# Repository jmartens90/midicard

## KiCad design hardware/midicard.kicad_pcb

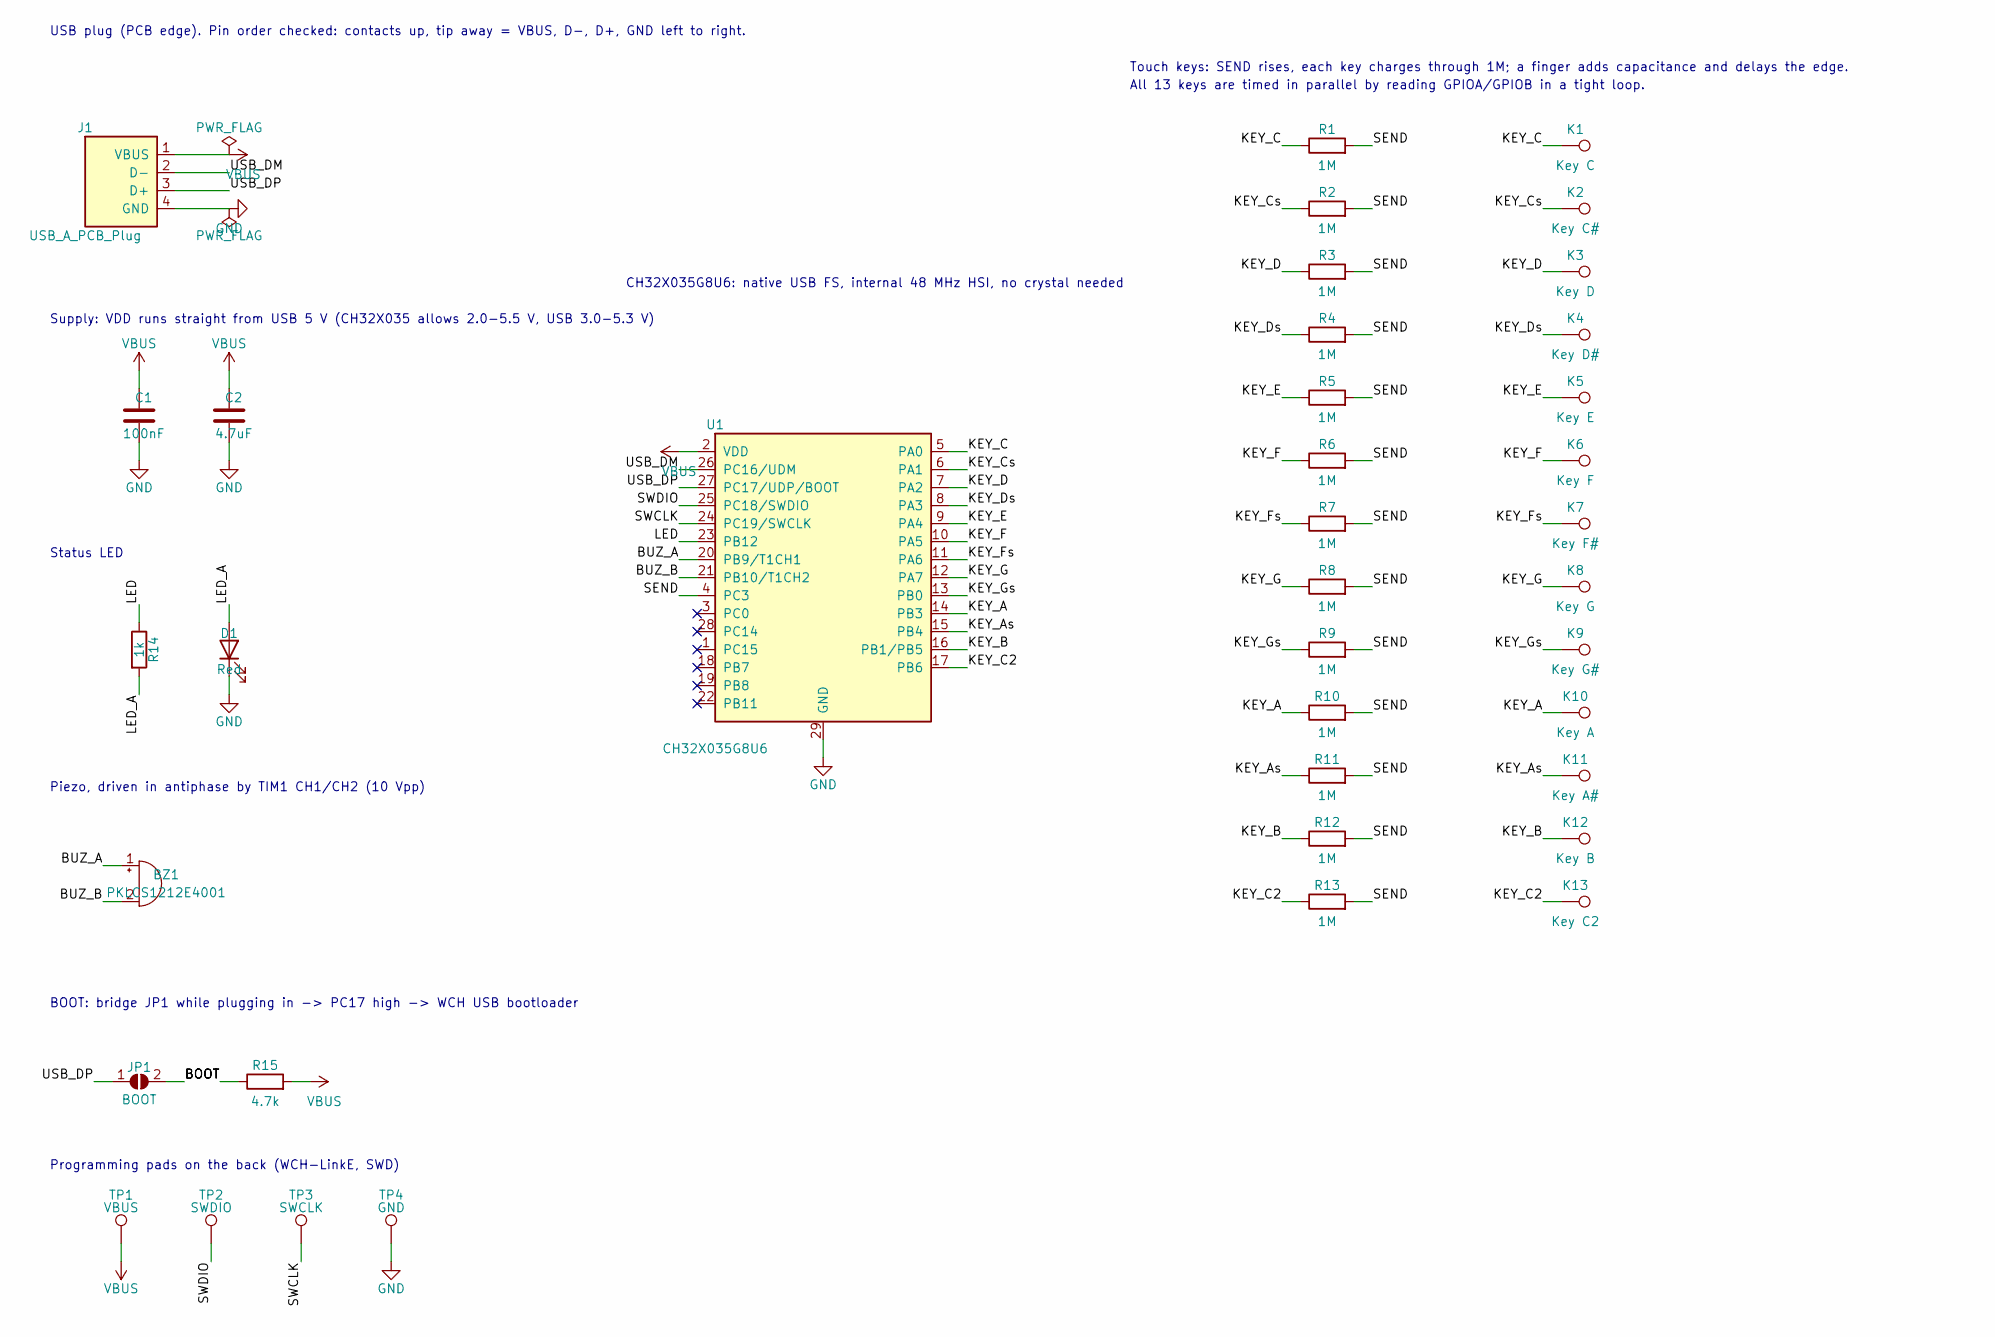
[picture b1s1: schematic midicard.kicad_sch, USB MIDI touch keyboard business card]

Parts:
BZ1: PKLCS1212E4001; Buzzer_Murata_PKLCS1212E; LCSC C113159
C1: 100nF; C_0402_1005Metric; LCSC C1525
C2: 4.7uF; C_0603_1608Metric; LCSC C19666
D1: Red; LED_0603_1608Metric; LCSC C2286
J1: USB_A_PCB_Plug
JP1: BOOT; SolderJumper-2_P1.3mm_Open_RoundedPad1.0x1.5mm
K1: Key C; TouchKey_KEY_C
K2: Key C#; TouchKey_KEY_Cs
K3: Key D; TouchKey_KEY_D
K4: Key D#; TouchKey_KEY_Ds
K5: Key E; TouchKey_KEY_E
K6: Key F; TouchKey_KEY_F
K7: Key F#; TouchKey_KEY_Fs
K8: Key G; TouchKey_KEY_G
K9: Key G#; TouchKey_KEY_Gs
K10: Key A; TouchKey_KEY_A
K11: Key A#; TouchKey_KEY_As
K12: Key B; TouchKey_KEY_B
K13: Key C2; TouchKey_KEY_C2
R1, R2, R3, R4, R5, R6, R7, R8, R9, R10, R11, R12, R13: 1M; R_0402_1005Metric; LCSC C26083
R14: 1k; R_0402_1005Metric; LCSC C11702
R15: 4.7k; R_0402_1005Metric; LCSC C25900
TP1: VBUS; TestPoint_Pad_D1.0mm
TP2: SWDIO; TestPoint_Pad_D1.0mm
TP3: SWCLK; TestPoint_Pad_D1.0mm
TP4: GND; TestPoint_Pad_D1.0mm
U1: CH32X035G8U6; QFN-28-1EP_4x4mm_P0.4mm_EP2.6x2.6mm; LCSC C7437027

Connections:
BOOT: JP1.2 (B), R15.1
BUZ_A: BZ1.1 (+), U1.20 (PB9/T1CH1)
BUZ_B: BZ1.2 (-), U1.21 (PB10/T1CH2)
GND: C1.2, C2.2, D1.1 (K), J1.4 (GND), TP4.1, U1.29 (GND)
KEY_A: K10.1, R10.1, U1.14 (PB3)
KEY_As: K11.1, R11.1, U1.15 (PB4)
KEY_B: K12.1, R12.1, U1.16 (PB1/PB5)
KEY_C: K1.1, R1.1, U1.5 (PA0)
KEY_C2: K13.1, R13.1, U1.17 (PB6)
KEY_Cs: K2.1, R2.1, U1.6 (PA1)
KEY_D: K3.1, R3.1, U1.7 (PA2)
KEY_Ds: K4.1, R4.1, U1.8 (PA3)
KEY_E: K5.1, R5.1, U1.9 (PA4)
KEY_F: K6.1, R6.1, U1.10 (PA5)
KEY_Fs: K7.1, R7.1, U1.11 (PA6)
KEY_G: K8.1, R8.1, U1.12 (PA7)
KEY_Gs: K9.1, R9.1, U1.13 (PB0)
LED: R14.1, U1.23 (PB12)
LED_A: D1.2 (A), R14.2
SEND: R1.2, R2.2, R3.2, R4.2, R5.2, R6.2, R7.2, R8.2, R9.2, R10.2, R11.2, R12.2, R13.2, U1.4 (PC3)
SWCLK: TP3.1, U1.24 (PC19/SWCLK)
SWDIO: TP2.1, U1.25 (PC18/SWDIO)
USB_DM: J1.2 (D-), U1.26 (PC16/UDM)
USB_DP: J1.3 (D+), JP1.1 (A), U1.27 (PC17/UDP/BOOT)
VBUS: C1.1, C2.1, J1.1 (VBUS), R15.2, TP1.1, U1.2 (VDD)

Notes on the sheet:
USB plug (PCB edge). Pin order checked: contacts up, tip away = VBUS, D-, D+, GND left to right.
Supply: VDD runs straight from USB 5 V (CH32X035 allows 2.0-5.5 V, USB 3.0-5.3 V)
Status LED
Piezo, driven in antiphase by TIM1 CH1/CH2 (10 Vpp)
BOOT: bridge JP1 while plugging in -> PC17 high -> WCH USB bootloader
Programming pads on the back (WCH-LinkE, SWD)
CH32X035G8U6: native USB FS, internal 48 MHz HSI, no crystal needed
Touch keys: SEND rises, each key charges through 1M; a finger adds capacitance and delays the edge.
All 13 keys are timed in parallel by reading GPIOA/GPIOB in a tight loop.

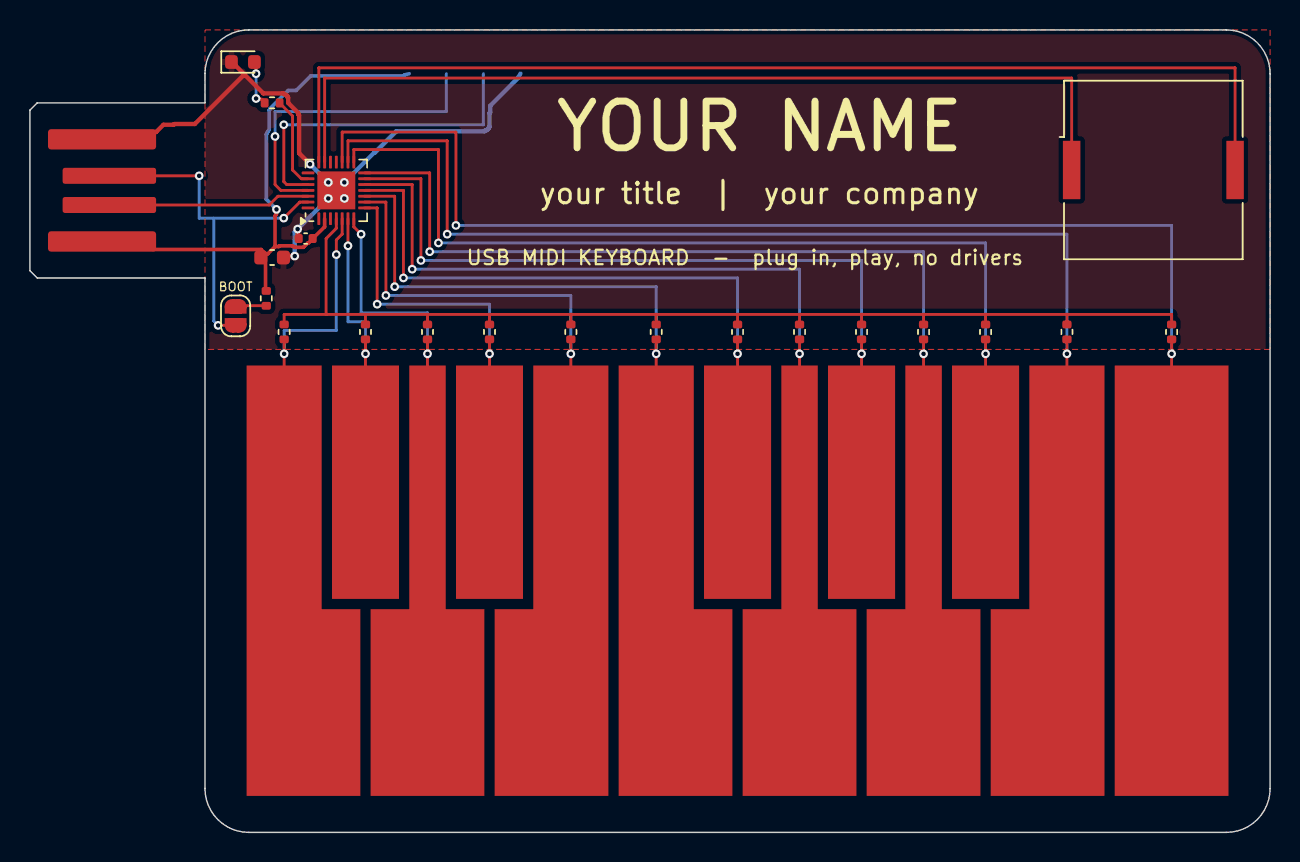
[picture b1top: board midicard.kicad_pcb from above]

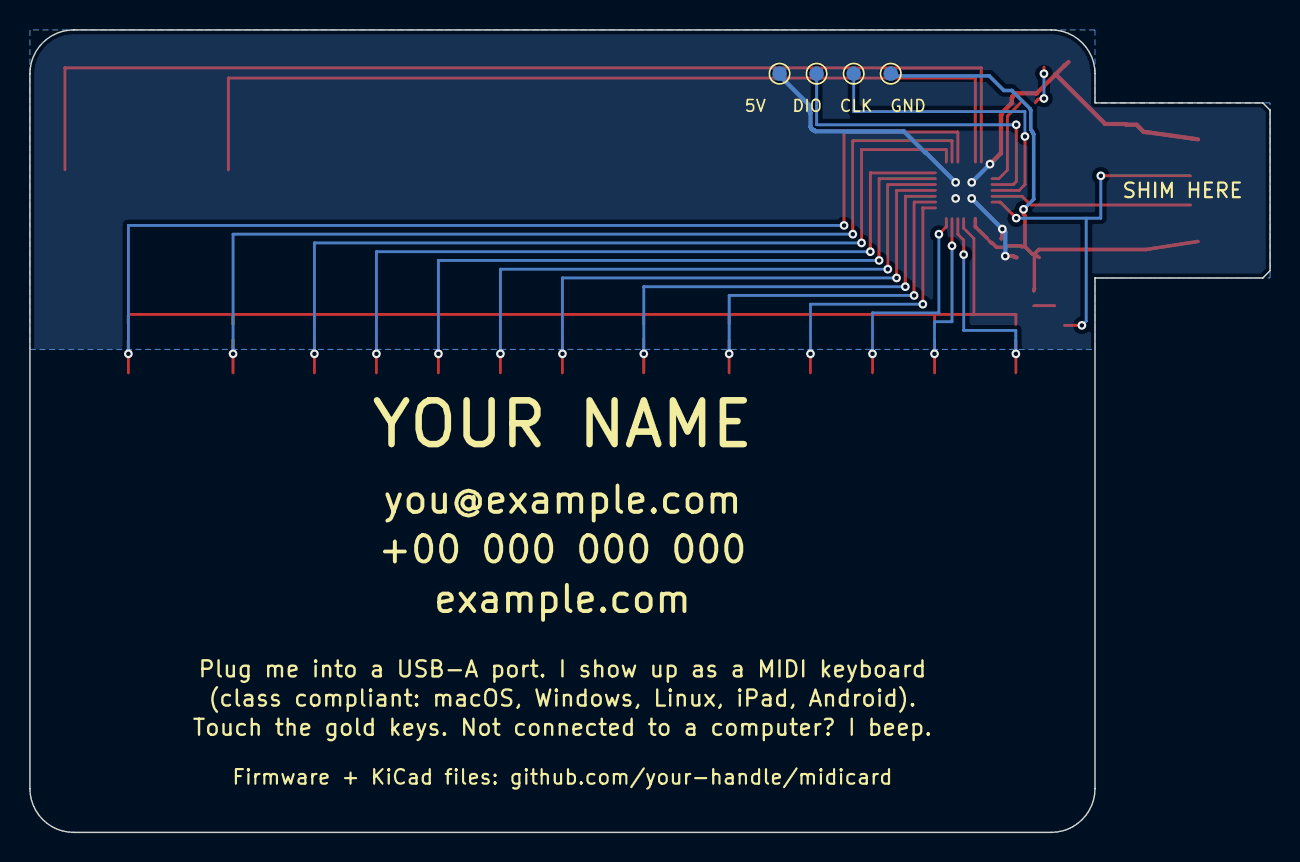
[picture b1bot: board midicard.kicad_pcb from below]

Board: 2 copper layers, 85.0 x 55.0 mm, 39 parts (4 on the bottom side), 25 nets.

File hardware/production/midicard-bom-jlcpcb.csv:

Comment,Designator,Footprint,LCSC Part #
PKLCS1212E4001,BZ1,Buzzer_Murata_PKLCS1212E,C113159
100nF,C1,C_0402_1005Metric,C1525
4.7uF,C2,C_0603_1608Metric,C19666
Red,D1,LED_0603_1608Metric,C2286
1M,"R1,R2,R3,R4,R5,R6,R7,R8,R9,R10,R11,R12,R13",R_0402_1005Metric,C26083
1k,R14,R_0402_1005Metric,C11702
4.7k,R15,R_0402_1005Metric,C25900
CH32X035G8U6,U1,QFN-28-1EP_4x4mm_P0.4mm_EP2.6x2.6mm,C7437027

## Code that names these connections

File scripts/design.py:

"""Single source of truth for the MIDI card: parts, footprints, nets, LCSC numbers.

Both the schematic generator (gen_schematic.py) and the PCB generator
(gen_pcb.py) import this file, so the schematic and the board cannot drift apart.
"""

# Touch keys, left to right on the card, with the MCU pin that senses each one.
# The firmware (firmware/keys.h) uses the same table.
KEYS = [
    # name,  MIDI offset, black?, MCU pin number, port pin
    ("C",   0, False,  5, "PA0"),
    ("C#",  1, True,   6, "PA1"),
    ("D",   2, False,  7, "PA2"),
    ("D#",  3, True,   8, "PA3"),
    ("E",   4, False,  9, "PA4"),
    ("F",   5, False, 10, "PA5"),
    ("F#",  6, True,  11, "PA6"),
    ("G",   7, False, 12, "PA7"),
    ("G#",  8, True,  13, "PB0"),
    ("A",   9, False, 14, "PB3"),
    ("A#", 10, True,  15, "PB4"),
    ("B",  11, False, 16, "PB1"),
    ("C2", 12, False, 17, "PB6"),
]


def key_net(name):
    return "KEY_" + name.replace("#", "s")


# CH32X035G8U6 (QFN-28, 4x4 mm). Pin number -> (name shown in the symbol, net)
MCU_PINS = {
    1: ("PC15", None),
    2: ("VDD", "VBUS"),
    3: ("PC0", None),
    4: ("PC3", "SEND"),
    18: ("PB7", None),
    19: ("PB8", None),
    20: ("PB9/T1CH1", "BUZ_A"),
    21: ("PB10/T1CH2", "BUZ_B"),
    22: ("PB11", None),
    23: ("PB12", "LED"),
    24: ("PC19/SWCLK", "SWCLK"),
    25: ("PC18/SWDIO", "SWDIO"),
    26: ("PC16/UDM", "USB_DM"),
    27: ("PC17/UDP/BOOT", "USB_DP"),
    28: ("PC14", None),
    29: ("GND", "GND"),
}
for _n, _off, _blk, _pin, _port in KEYS:
    MCU_PINS[_pin] = ("PB1/PB5" if _port == "PB1" else _port, key_net(_n))

# Parts. pins: pad number -> net.  lcsc None = not assembled by JLCPCB.
PARTS = []


def part(ref, value, lib_id, footprint, pins, lcsc=None, desc="", dnp=False):
    PARTS.append(dict(ref=ref, value=value, lib_id=lib_id, footprint=footprint,
                      pins=pins, lcsc=lcsc, desc=desc, dnp=dnp))


part("U1", "CH32X035G8U6", "midicard:CH32X035G8U6",
     "midicard:QFN-28-1EP_4x4mm_P0.4mm_EP2.6x2.6mm",
     {str(k): v[1] for k, v in MCU_PINS.items()}, "C7437027",
     "RISC-V MCU, USB full speed device, runs from 5 V, no crystal")
part("J1", "USB_A_PCB_Plug", "midicard:USB_A_Plug", "midicard:USB_A_PCB_Plug",
     {"1": "VBUS", "2": "USB_DM", "3": "USB_DP", "4": "GND"}, None,
     "USB-A plug formed by the PCB edge (gold contacts, no part)")
part("C1", "100nF", "Device:C", "Capacitor_SMD:C_0402_1005Metric",
     {"1": "VBUS", "2": "GND"}, "C1525", "16 V X7R")
part("C2", "4.7uF", "Device:C", "Capacitor_SMD:C_0603_1608Metric",
     {"1": "VBUS", "2": "GND"}, "C19666", "16 V X5R")
part("R14", "1k", "Device:R", "Resistor_SMD:R_0402_1005Metric",
     {"1": "LED", "2": "LED_A"}, "C11702", "LED current limit")
part("D1", "Red", "Device:LED", "LED_SMD:LED_0603_1608Metric",
     {"1": "GND", "2": "LED_A"}, "C2286", "status LED (pad 1 = cathode)")
part("BZ1", "PKLCS1212E4001", "Device:Buzzer", "Buzzer_Beeper:Buzzer_Murata_PKLCS1212E",
     {"1": "BUZ_A", "2": "BUZ_B"}, "C113159",
     "passive piezo, driven push-pull from two pins")
part("R15", "4.7k", "Device:R", "Resistor_SMD:R_0402_1005Metric",
     {"1": "BOOT", "2": "VBUS"}, "C25900", "boot pull-up for USB bootloader")
part("JP1", "BOOT", "Jumper:SolderJumper_2_Open",
     "Jumper:SolderJumper-2_P1.3mm_Open_RoundedPad1.0x1.5mm",
     {"1": "USB_DP", "2": "BOOT"}, None,
     "bridge with tweezers while plugging in = USB bootloader")
for i, (n, off, blk, pin, port) in enumerate(KEYS):
    part("R%d" % (i + 1), "1M", "Device:R", "Resistor_SMD:R_0402_1005Metric",
         {"1": key_net(n), "2": "SEND"}, "C26083", "touch charge resistor")
for i, (n, off, blk, pin, port) in enumerate(KEYS):
    part("K%d" % (i + 1), "Key " + n, "Connector:TestPoint",
         "midicard:TouchKey_" + key_net(n), {"1": key_net(n)}, None,
         "copper touch key")
for ref, net in (("TP1", "VBUS"), ("TP2", "SWDIO"), ("TP3", "SWCLK"), ("TP4", "GND")):
    part(ref, net, "Connector:TestPoint", "TestPoint:TestPoint_Pad_D1.0mm",
         {"1": net}, None, "programming pad (back side)")


def nets():
    out = {}
    for p in PARTS:
        for pad, net in p["pins"].items():
            if net:
                out.setdefault(net, []).append((p["ref"], pad))
    return out


if __name__ == "__main__":
    for n, conns in sorted(nets().items()):
        print(n, conns)
